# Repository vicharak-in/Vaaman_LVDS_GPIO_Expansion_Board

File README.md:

# Vaaman_UART_Expansion_Board

GPIO HAT 1:

LVDS RX and TX from Vaaman configure as a GPIO of this HAT. total 80 GPIOs are availabe in HAT can be configure form Vaaman LVDS.

voltage level of signal: 3.3V

Level translator Part number: TXB0108DQSR

LVDS connector part number: DF40C-60DP-0.4V(51)

Vaaman and HAT Connection: Flex cable

Power input: Vaaman Header 

NOT tested Yet(GPIO HAT 1).

GPIO HAT 2:

LVDS RX and TX from Vaaman configure as a GPIO of this HAT. total 80 GPIOs are availabe in HAT can be configure form Vaaman LVDS.

voltage level of signal: 3.3V & 1.8V (using jumper)

Level translator Part number: TXB0108DQSR

LVDS connector part number: DF40C-60DP-0.4V(51)

Vaaman and HAT Connection: Flex cable

Power input: Vaaman Header or Type-C 

Power up instructions:

Vaaman LVDS GPIO HAT can Power by two Options: 

Option 1: Using Female to Female Jumper From Vaaman Header to GPIO Hat Header

Vaaman Header 5V and GND:

GPIO HAT Header:

Working Properly.

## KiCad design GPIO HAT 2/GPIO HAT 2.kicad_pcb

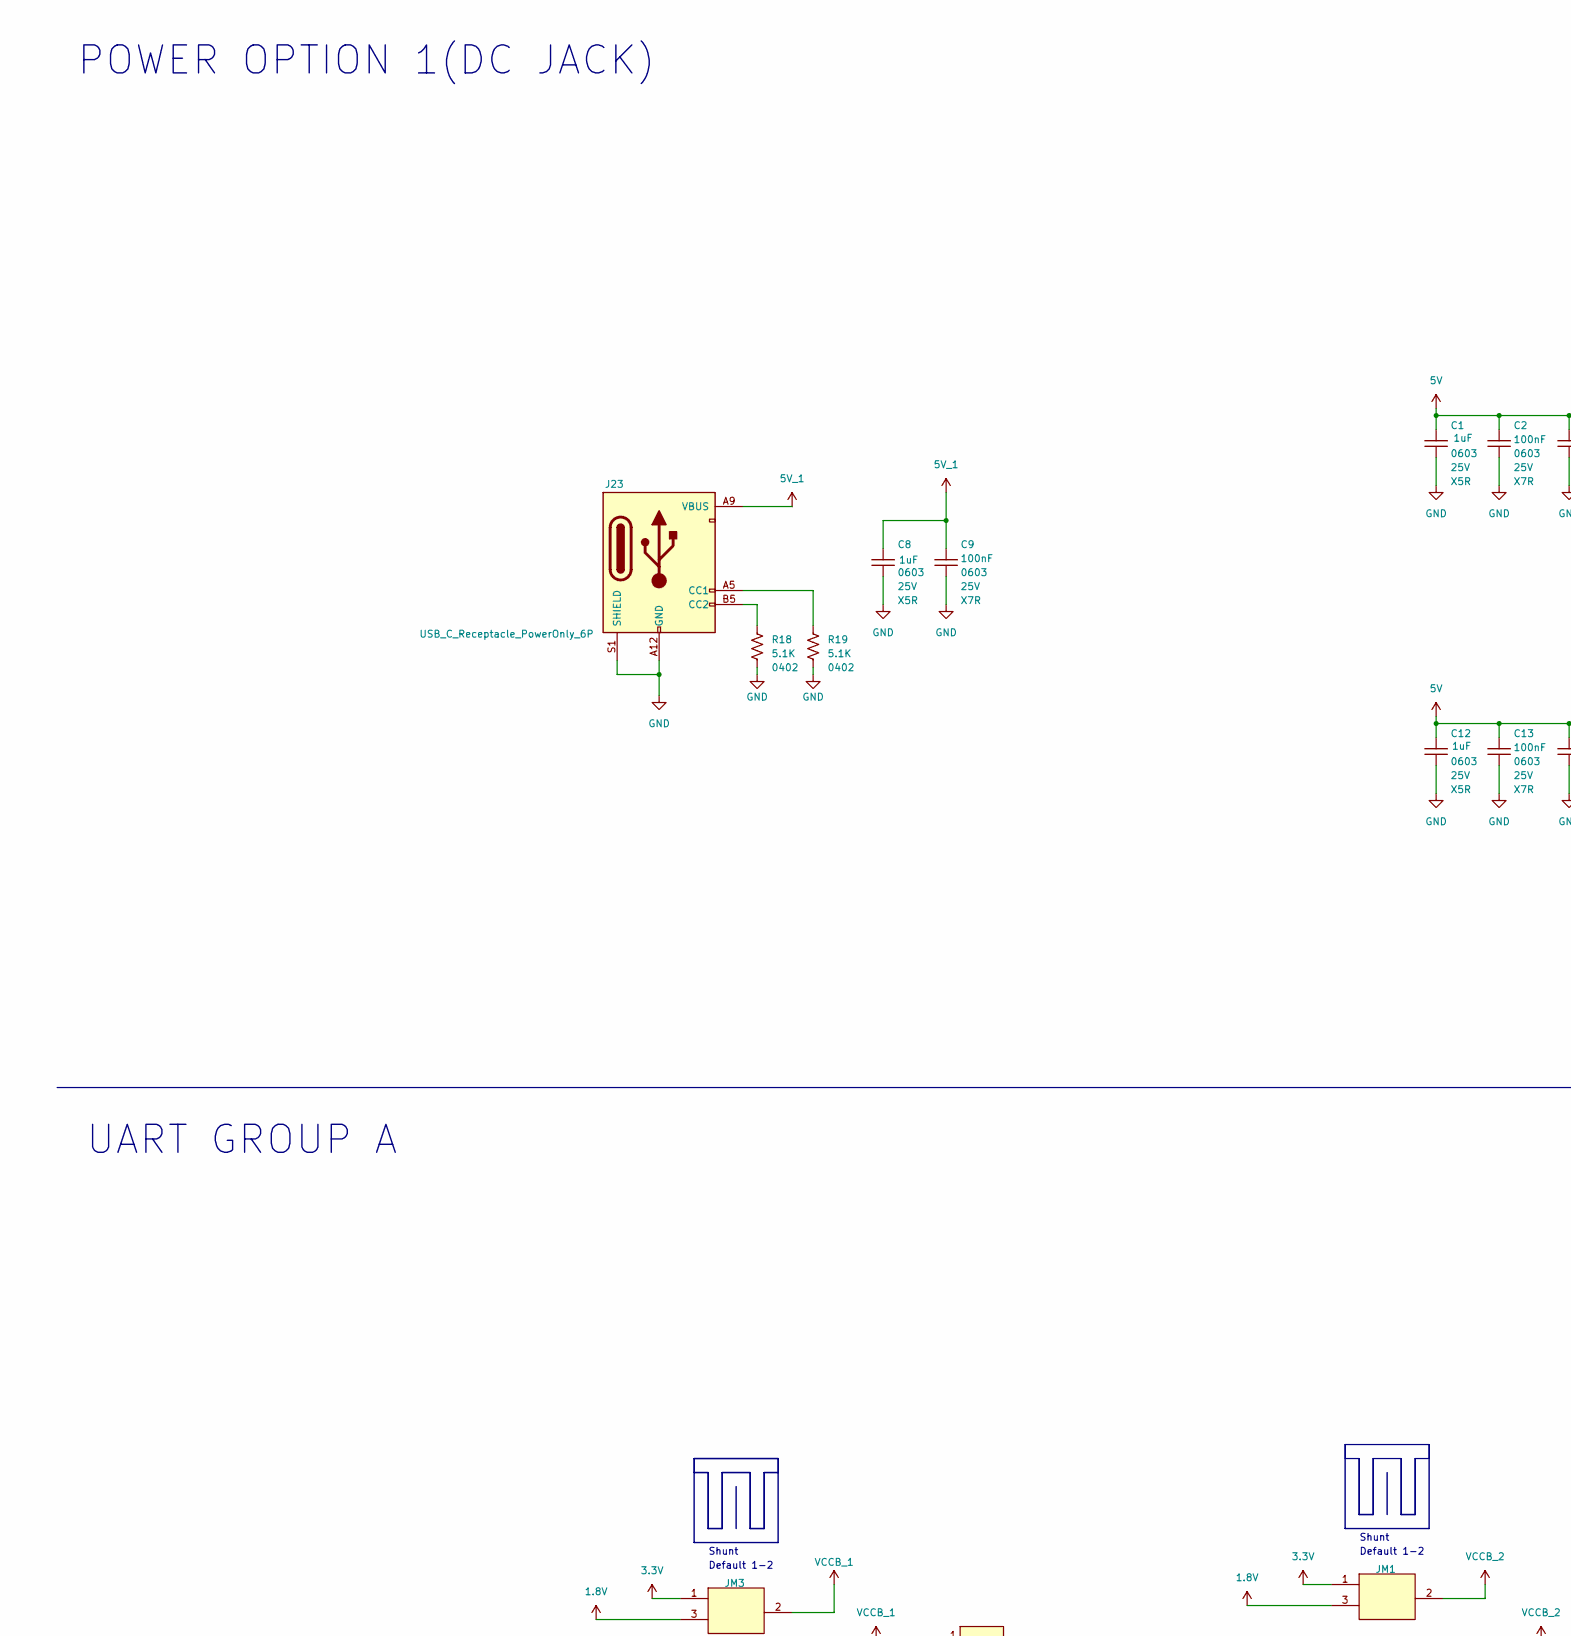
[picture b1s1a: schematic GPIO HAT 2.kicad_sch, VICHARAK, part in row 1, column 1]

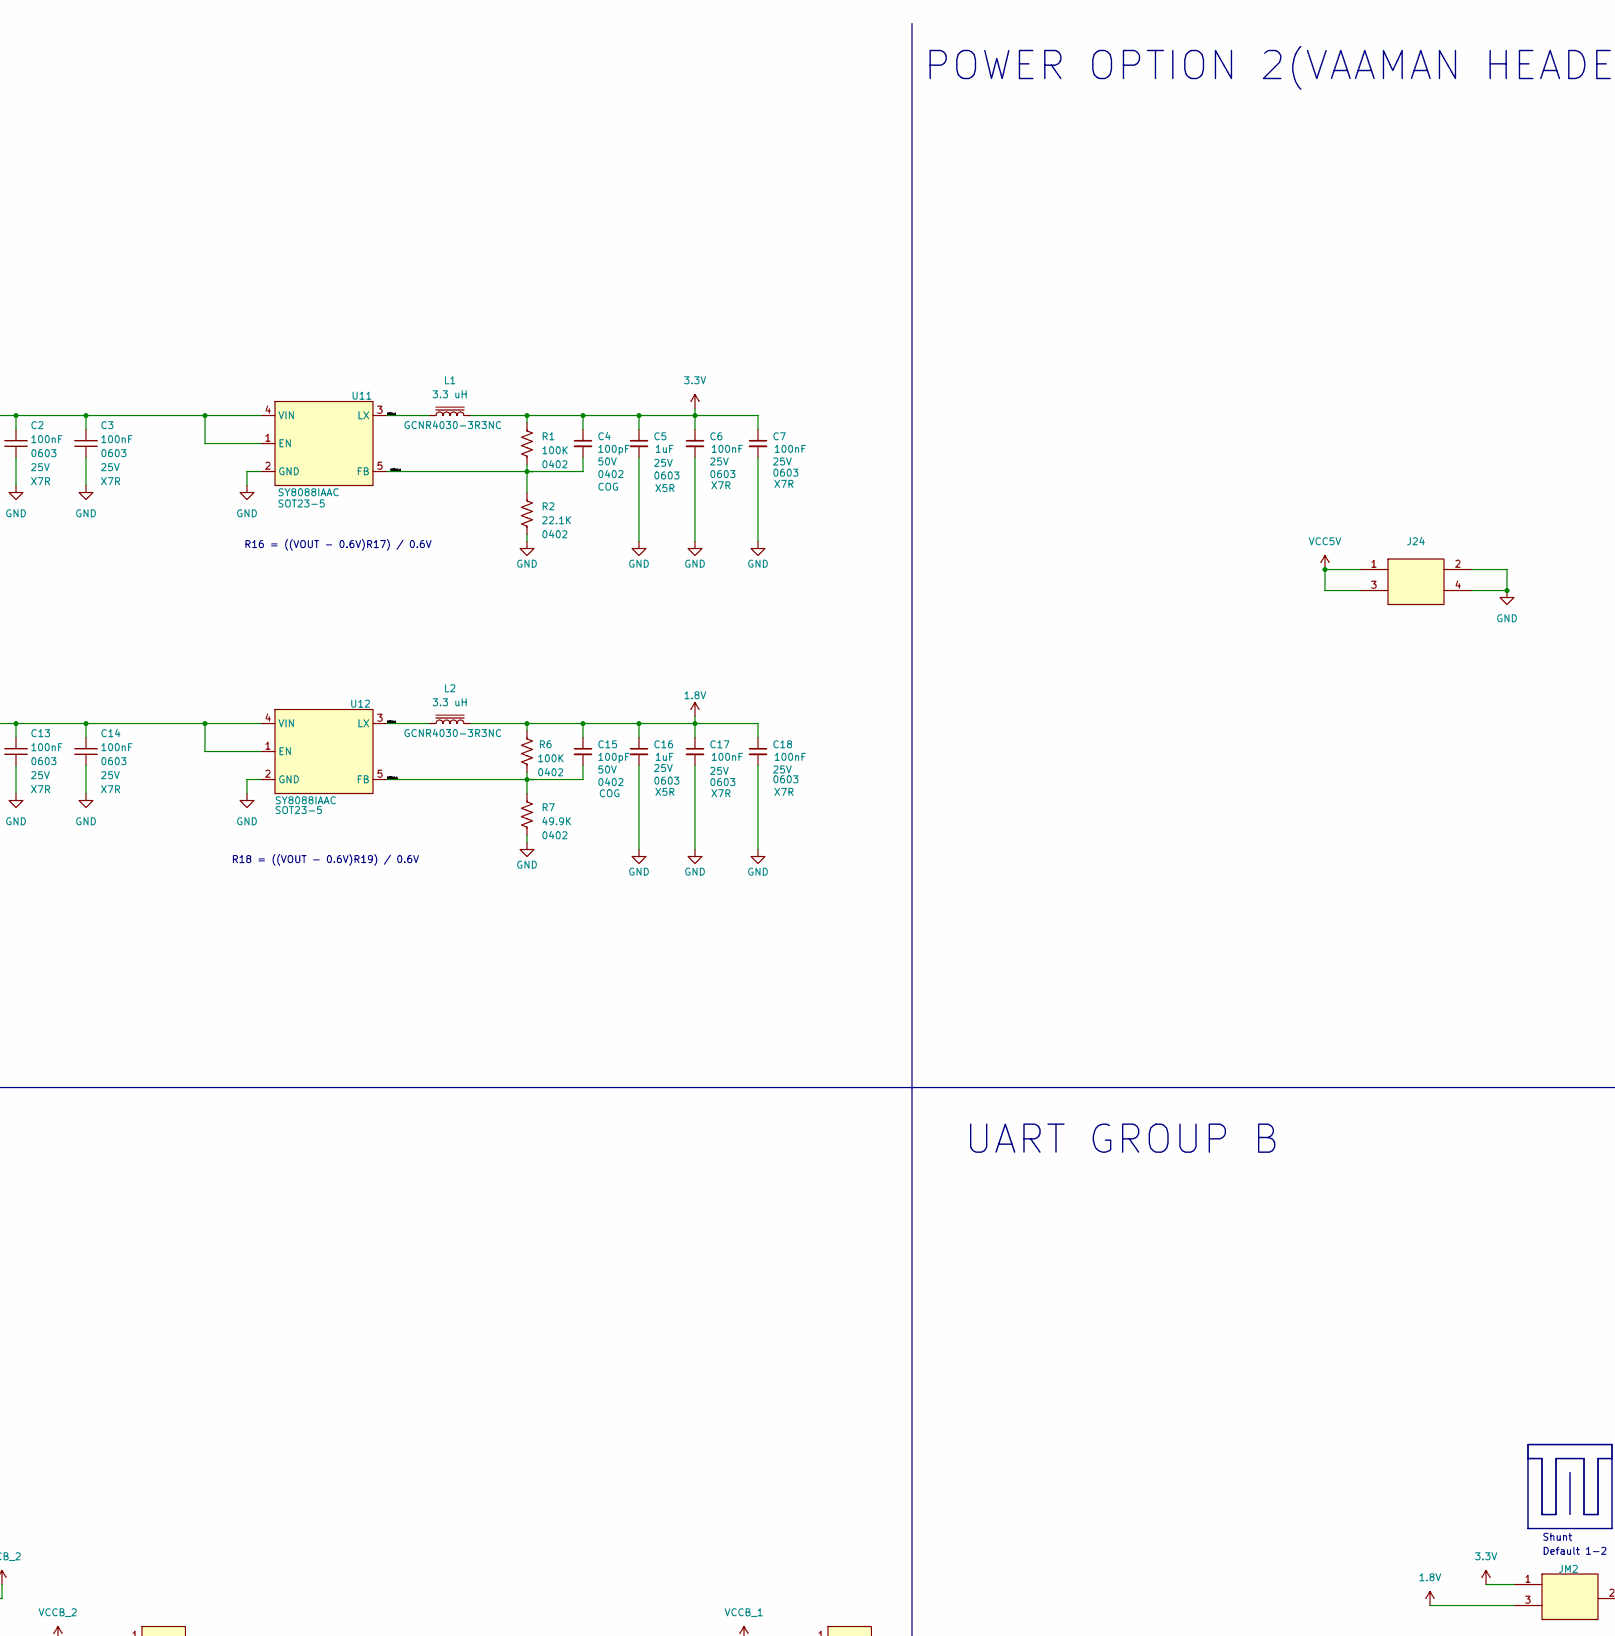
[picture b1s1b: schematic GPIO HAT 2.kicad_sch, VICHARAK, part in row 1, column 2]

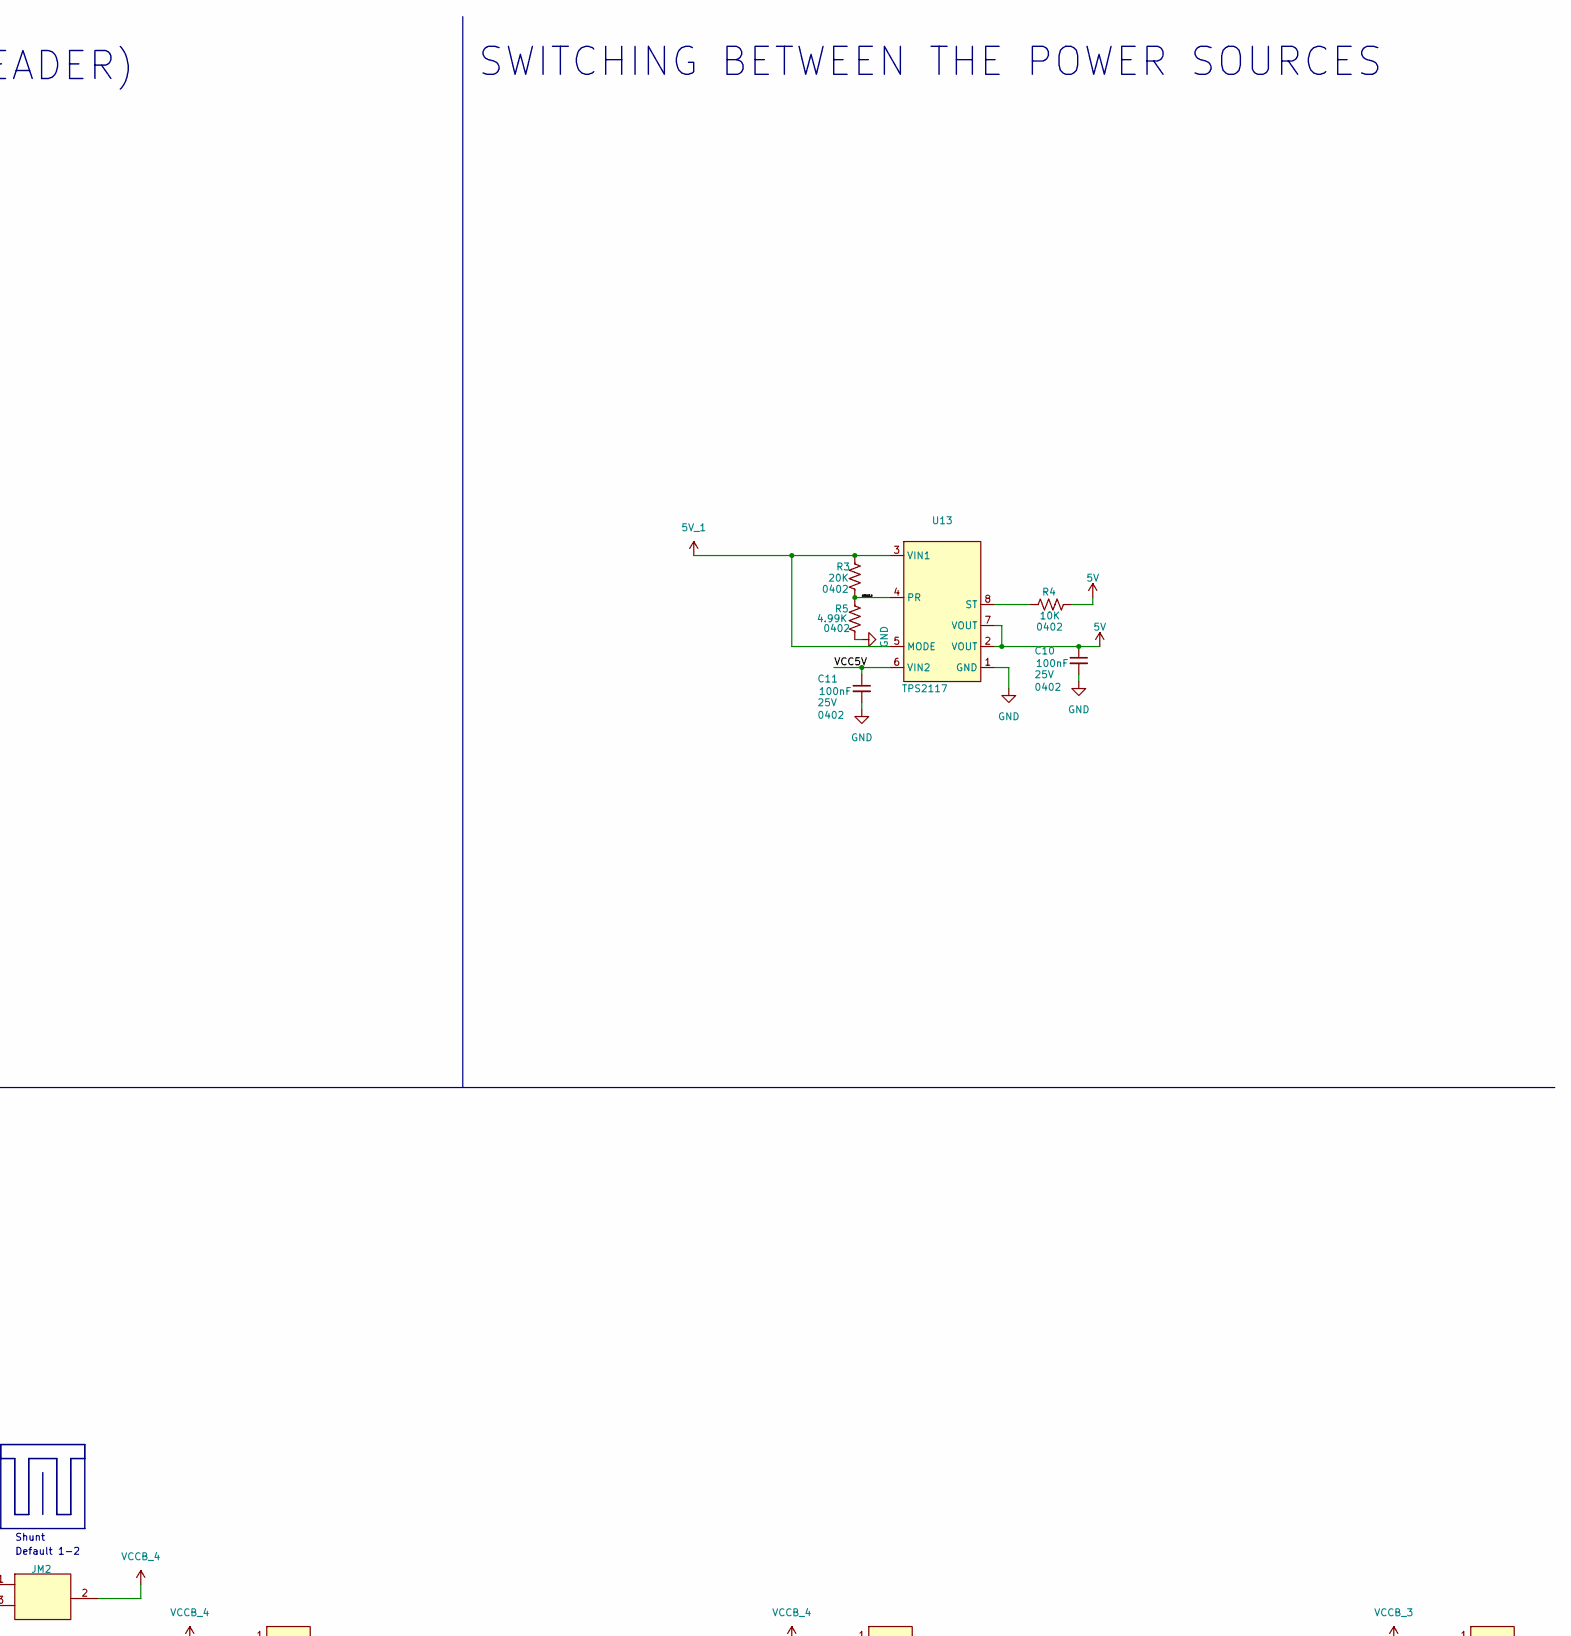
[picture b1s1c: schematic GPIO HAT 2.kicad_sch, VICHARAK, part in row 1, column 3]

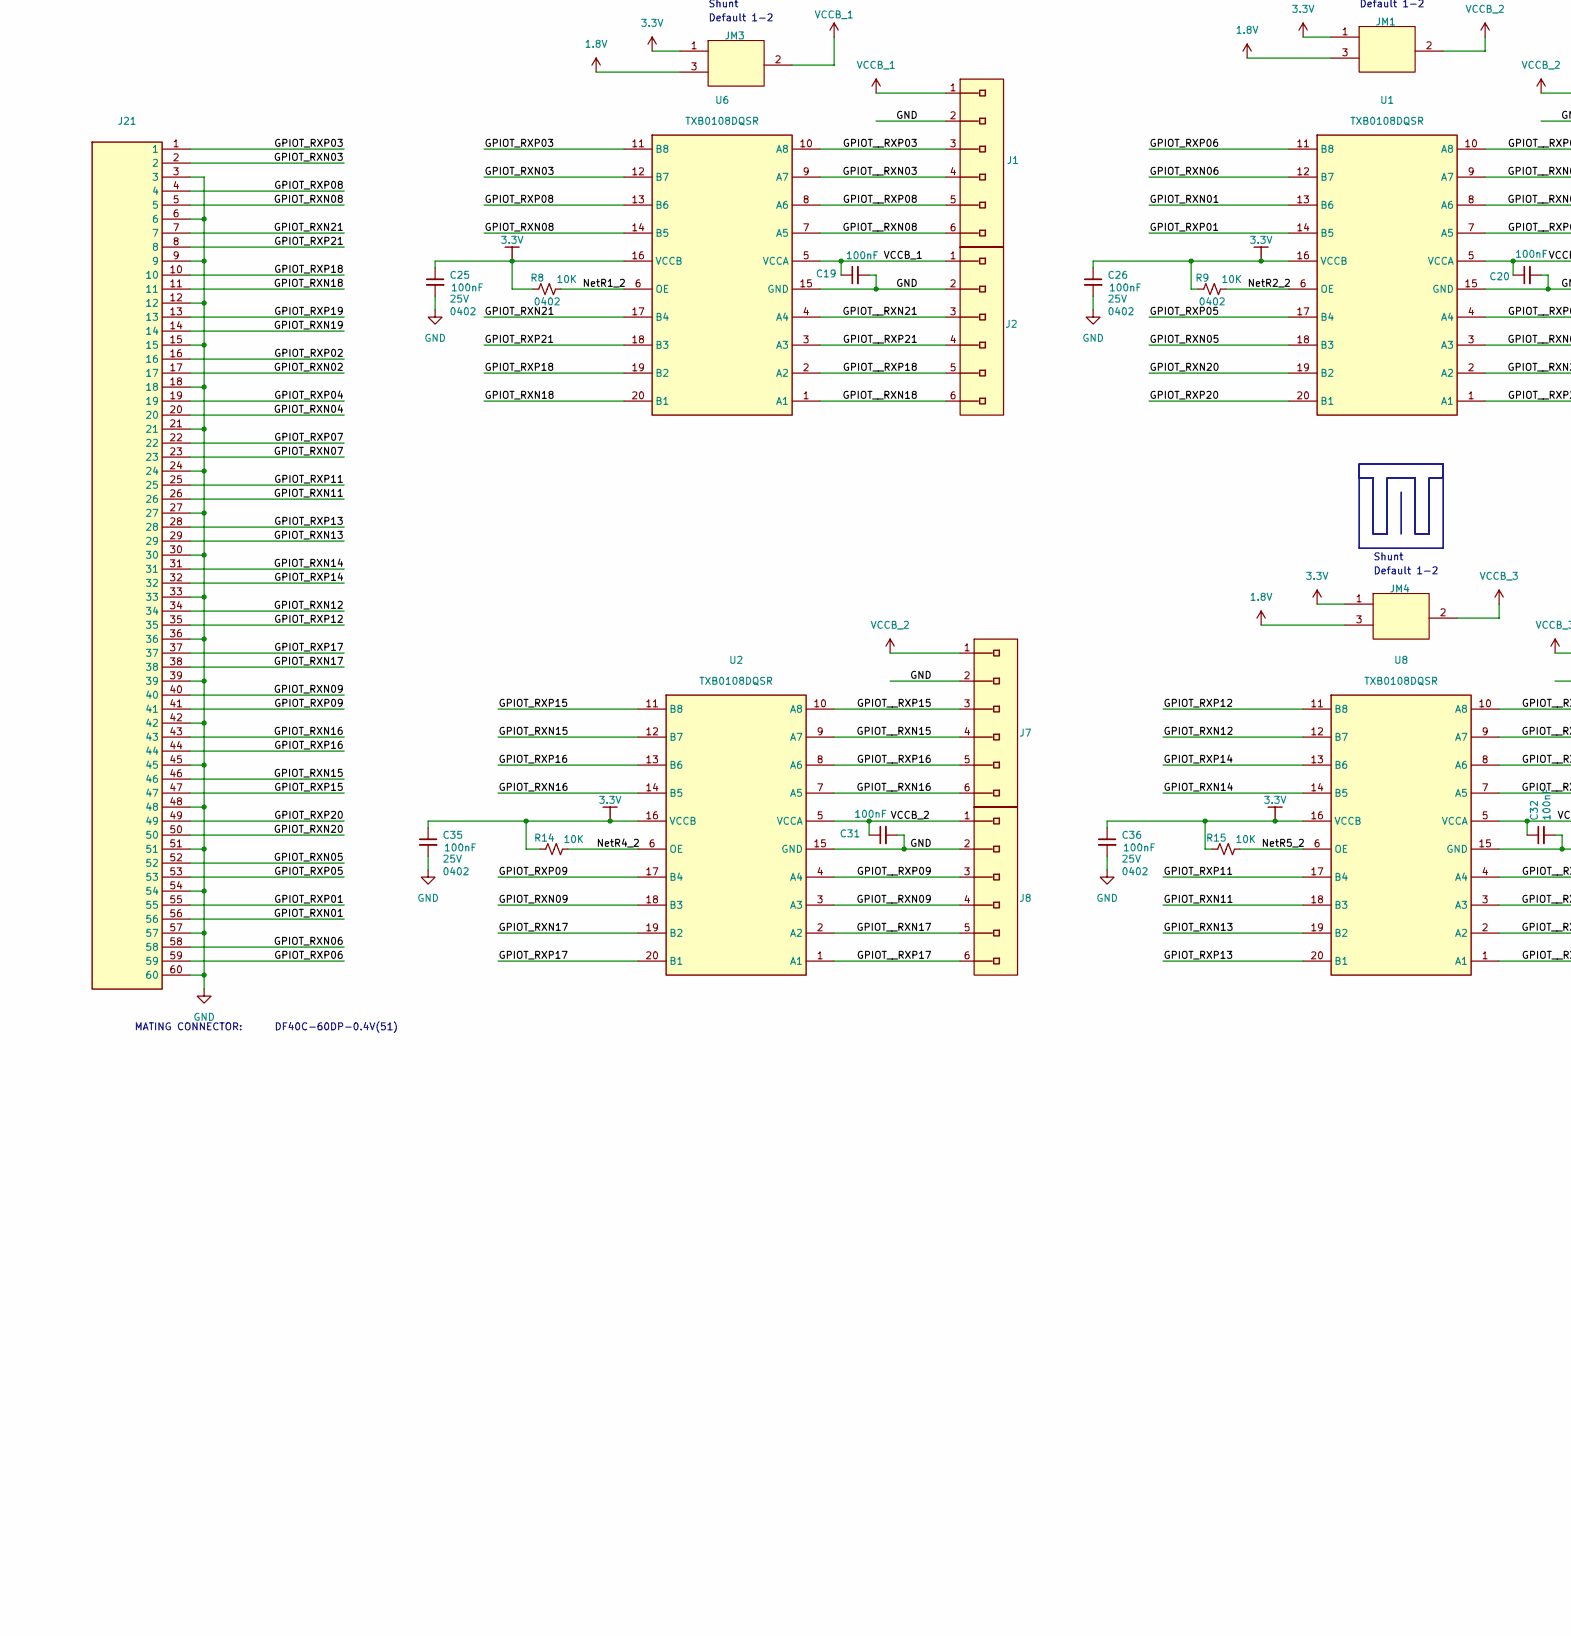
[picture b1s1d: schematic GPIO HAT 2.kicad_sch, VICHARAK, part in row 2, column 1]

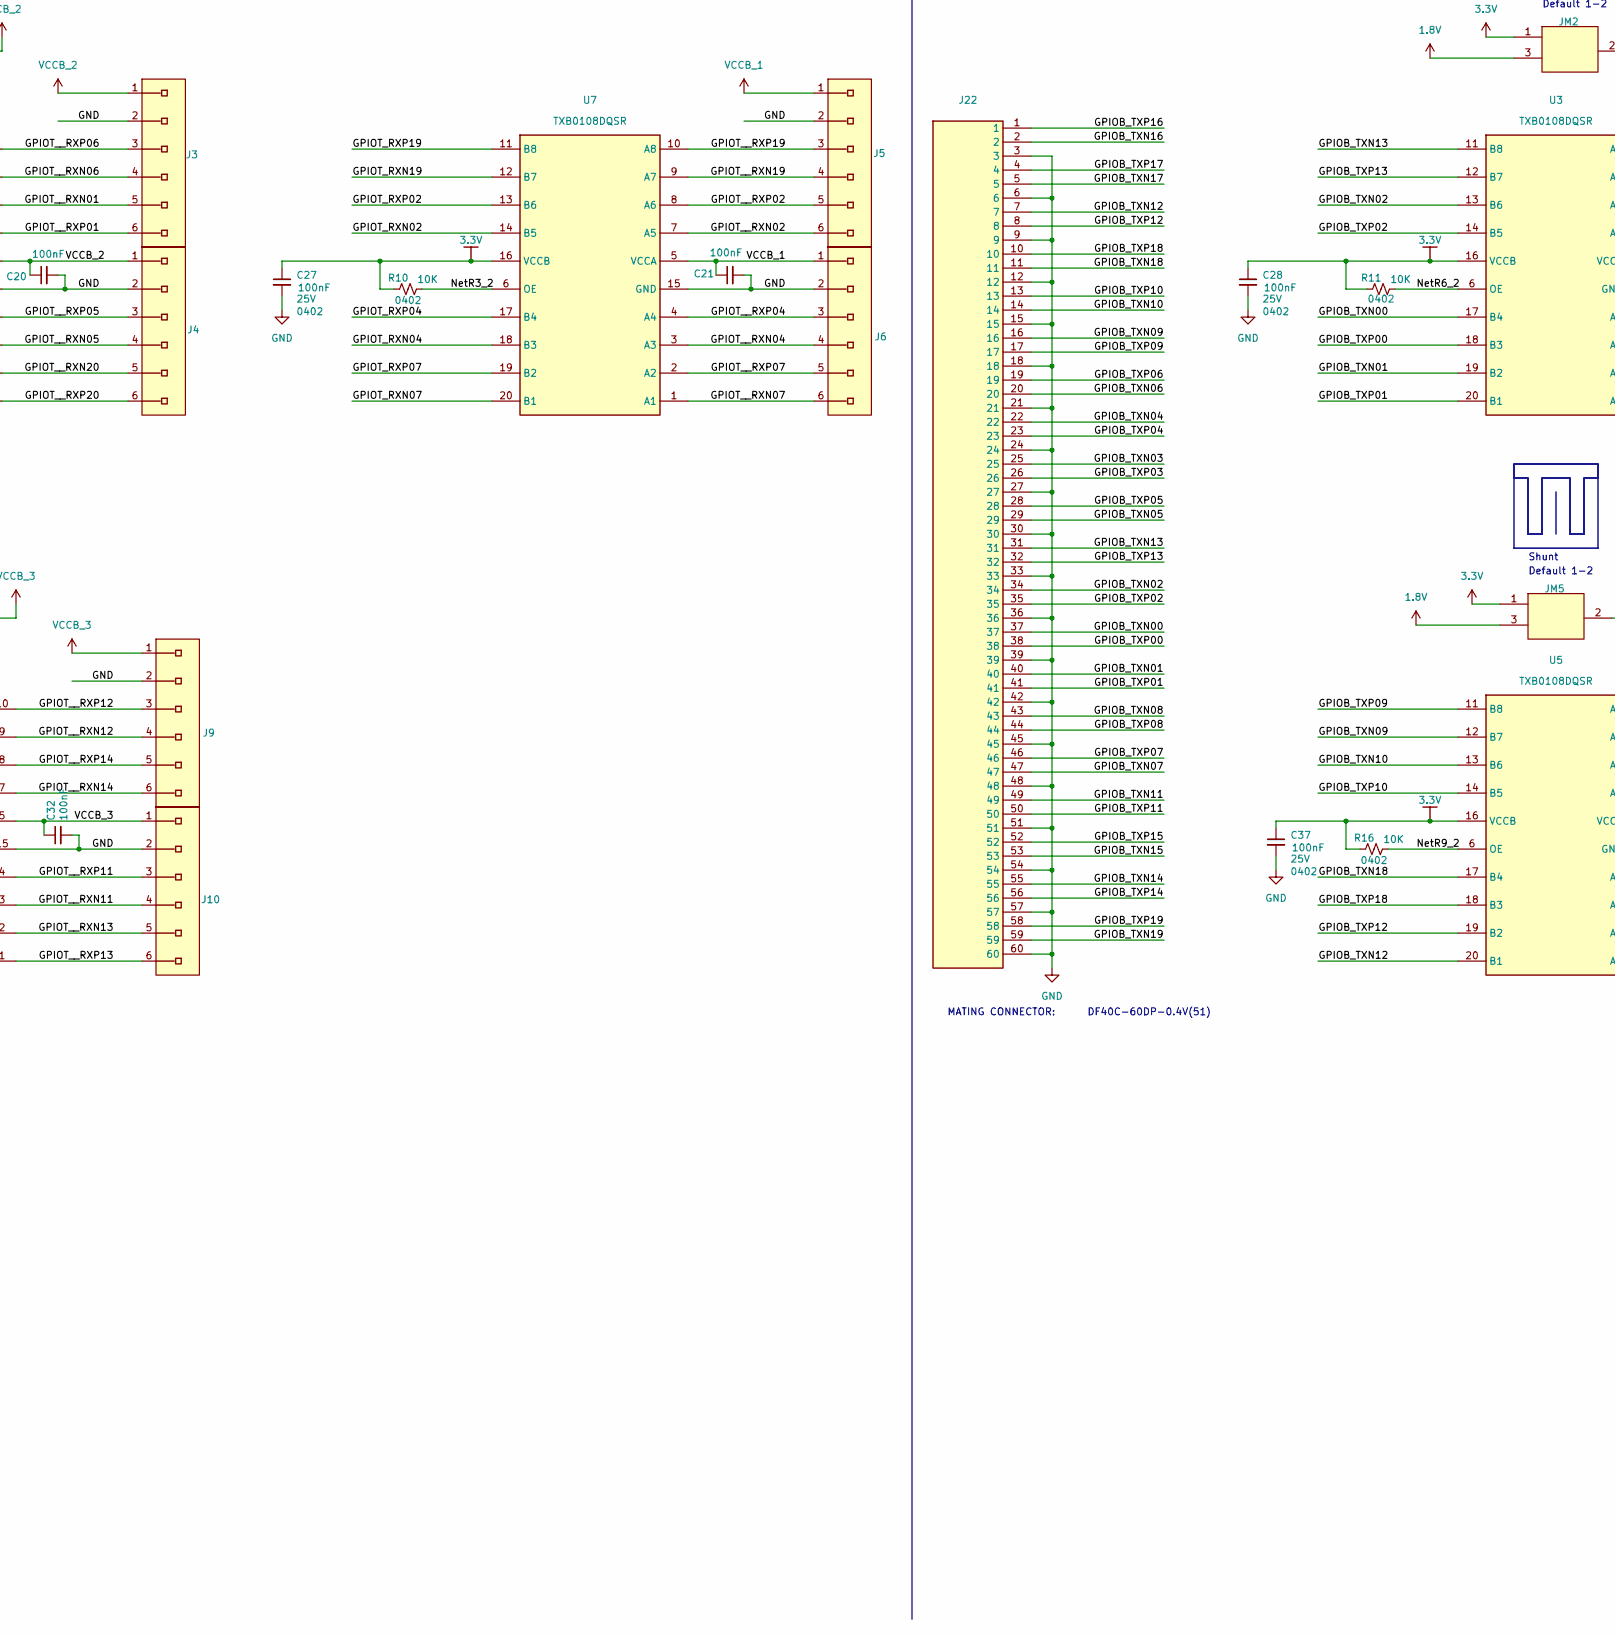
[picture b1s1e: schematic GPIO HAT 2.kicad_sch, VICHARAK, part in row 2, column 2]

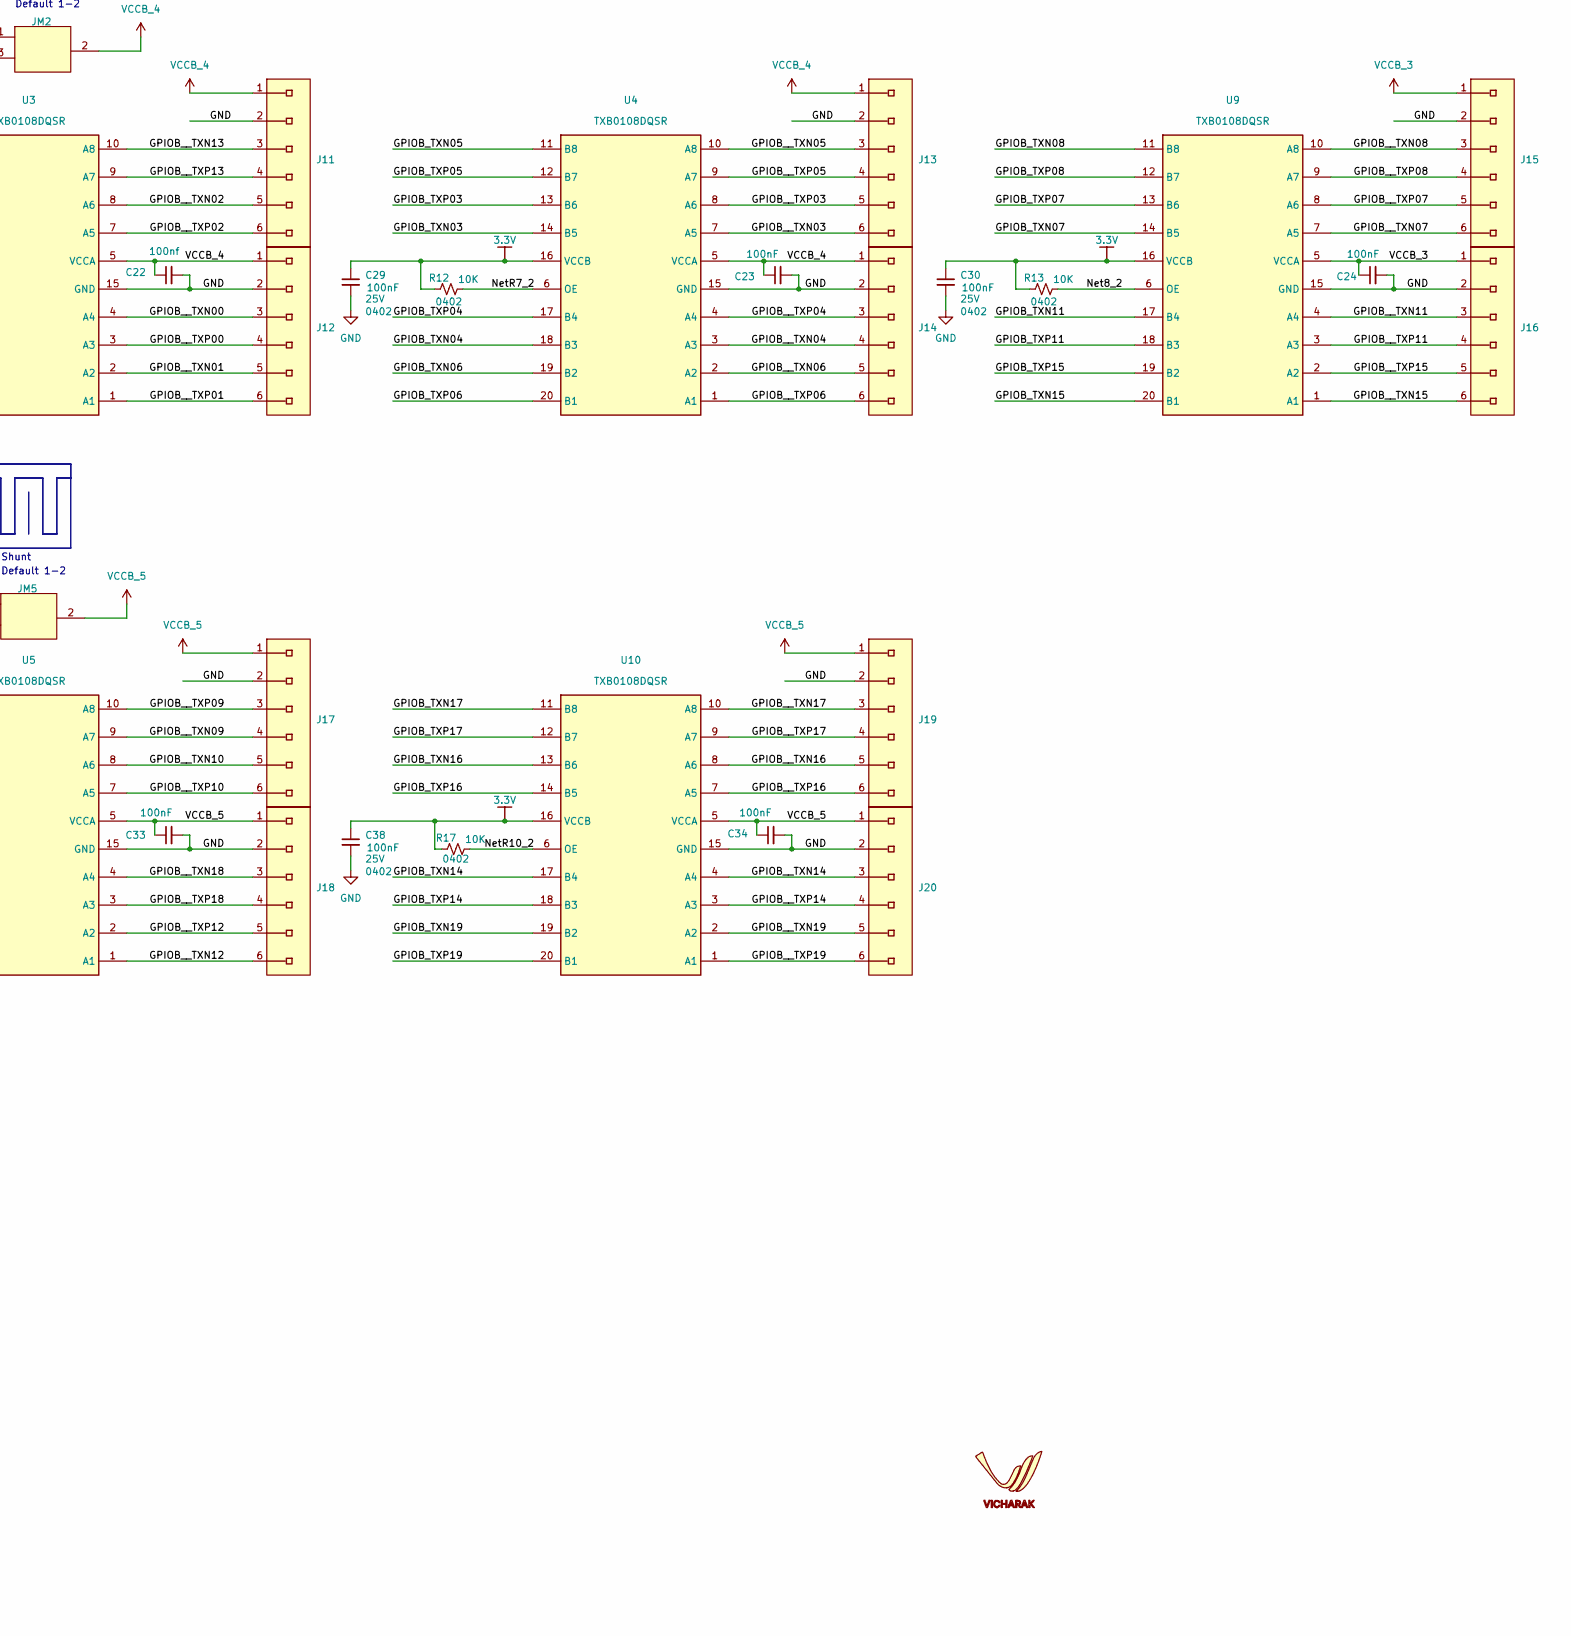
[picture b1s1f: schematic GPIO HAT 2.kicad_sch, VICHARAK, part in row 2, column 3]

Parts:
C1, C5, C8, C12, C16: 1uF; 0603_Cap; VOLTAGE 25V
C2, C3, C6, C7, C9, C13, C14, C17, C18: 100nF; 0603_Cap; VOLTAGE 25V
C4, C15: 100pF; 0402_Cap; VOLTAGE 50V
C10, C11, C19, C20, C21, C23, C24, C25, C26, C27, C28, C29, C30, C31, C32, C33, C34, C35, C36, C37, C38: 100nF; 0402_Cap; VOLTAGE 25V
C22: 100nf; 0402_Cap; VOLTAGE 25V
J1, J2, J3, J4, J5, J6, J7, J8, J9, J10, J11, J12, J13, J14, J15, J16, J17, J18, J19, J20: .; 01x06 HEADER
J21, J22: LVDS; Mouser Part Number 798-DF40C60DS0.4V51
J23: USB_C_Receptacle_PowerOnly_6P; USB_C_Receptacle_GCT_USB4125-xx-x-0190_6P_TopMnt_Horizontal; Manufacturer Part Number U262-061N-4BVC10
J24: 02x02; 02X02 HEADER
JM1, JM2, JM3, JM4, JM5: PinHeader_1x03_P2.54mm_Vertical
L1, L2: 3.3 uH; GCNR4030-3R3NC; Manufacturer Part Number GCNR4030-3R3NC
R1, R6: 100K; 0402_Res
R2: 22.1K; 0402_Res
R3: 20K; 0402_Res
R4, R8, R9, R10, R11, R12, R13, R14, R15, R16, R17: 10K; 0402_Res
R5: 4.99K; 0402_Res
R7: 49.9K; 0402_Res
R18, R19: 5.1K; 0402_Res
U1, U2, U3, U4, U5, U6, U7, U8, U9, U10: Manufacturer Part Number TXB0108DQSR
U11, U12: SY8088IAAC; Manufacturer Part Number SY8088IAAC
U13: TPS2117

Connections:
1.8V: C15.1, C16.1, C17.1, C18.1, JM1.3, JM2.3, JM3.3, JM4.3, JM5.3, L2.2, R6.1
3.3V: C4.1, C5.1, C6.1, C7.1, C25.1, C26.1, C27.1, C28.1, C29.1, C30.1, C35.1, C36.1, C37.1, C38.1, JM1.1, JM2.1, JM3.1, JM4.1, JM5.1, L1.2, R1.1, R8.1, R9.1, R10.1, R11.1, R12.1, R13.1, R14.1, R15.1, R16.1, R17.1, U1.16 (VCCB), U2.16 (VCCB), U3.16 (VCCB), U4.16 (VCCB), U5.16 (VCCB), U6.16 (VCCB), U7.16 (VCCB), U8.16 (VCCB), U9.16 (VCCB), U10.16 (VCCB)
5V: C1.1, C2.1, C3.1, C10.1, C12.1, C13.1, C14.1, R4.2, U11.1 (EN), U11.4 (VIN), U12.1 (EN), U12.4 (VIN), U13.2 (VOUT), U13.7 (VOUT)
5V_1: C8.1, C9.1, J23.A9 (VBUS), R3.2, U13.3 (VIN1), U13.5 (MODE)
/GPIOB_TXN00: J22.37, U3.17 (B4)
/GPIOB_TXN01: J22.40, U3.19 (B2)
/GPIOB_TXN02: J22.34, U3.13 (B6)
/GPIOB_TXN03: J22.25, U4.14 (B5)
/GPIOB_TXN04: J22.22, U4.18 (B3)
/GPIOB_TXN05: J22.29, U4.11 (B8)
/GPIOB_TXN06: J22.20, U4.19 (B2)
/GPIOB_TXN07: J22.47, U9.14 (B5)
/GPIOB_TXN08: J22.43, U9.11 (B8)
/GPIOB_TXN09: J22.16, U5.12 (B7)
/GPIOB_TXN10: J22.14, U5.13 (B6)
/GPIOB_TXN11: J22.49, U9.17 (B4)
/GPIOB_TXN12: J22.7, U5.20 (B1)
/GPIOB_TXN13: J22.31, U3.11 (B8)
/GPIOB_TXN14: J22.55, U10.17 (B4)
/GPIOB_TXN15: J22.53, U9.20 (B1)
/GPIOB_TXN16: J22.2, U10.13 (B6)
/GPIOB_TXN17: J22.5, U10.11 (B8)
/GPIOB_TXN18: J22.11, U5.17 (B4)
/GPIOB_TXN19: J22.59, U10.19 (B2)
/GPIOB_TXP00: J22.38, U3.18 (B3)
/GPIOB_TXP01: J22.41, U3.20 (B1)
/GPIOB_TXP02: J22.35, U3.14 (B5)
/GPIOB_TXP03: J22.26, U4.13 (B6)
/GPIOB_TXP04: J22.23, U4.17 (B4)
/GPIOB_TXP05: J22.28, U4.12 (B7)
/GPIOB_TXP06: J22.19, U4.20 (B1)
/GPIOB_TXP07: J22.46, U9.13 (B6)
/GPIOB_TXP08: J22.44, U9.12 (B7)
/GPIOB_TXP09: J22.17, U5.11 (B8)
/GPIOB_TXP10: J22.13, U5.14 (B5)
/GPIOB_TXP11: J22.50, U9.18 (B3)
/GPIOB_TXP12: J22.8, U5.19 (B2)
/GPIOB_TXP13: J22.32, U3.12 (B7)
/GPIOB_TXP14: J22.56, U10.18 (B3)
/GPIOB_TXP15: J22.52, U9.19 (B2)
/GPIOB_TXP16: J22.1, U10.14 (B5)
/GPIOB_TXP17: J22.4, U10.12 (B7)
/GPIOB_TXP18: J22.10, U5.18 (B3)
/GPIOB_TXP19: J22.58, U10.20 (B1)
/GPIOB__TXN00: J12.3, U3.4 (A4)
/GPIOB__TXN01: J12.5 (4), U3.2 (A2)
/GPIOB__TXN02: J11.5 (4), U3.8 (A6)
/GPIOB__TXN03: J13.6, U4.7 (A5)
/GPIOB__TXN04: J14.4, U4.3 (A3)
/GPIOB__TXN05: J13.3, U4.10 (A8)
/GPIOB__TXN06: J14.5 (4), U4.2 (A2)
/GPIOB__TXN07: J15.6, U9.7 (A5)
/GPIOB__TXN08: J15.3, U9.10 (A8)
/GPIOB__TXN09: J17.4, U5.9 (A7)
/GPIOB__TXN10: J17.5 (4), U5.8 (A6)
/GPIOB__TXN11: J16.3, U9.4 (A4)
/GPIOB__TXN12: J18.6, U5.1 (A1)
/GPIOB__TXN13: J11.3, U3.10 (A8)
/GPIOB__TXN14: J20.3, U10.4 (A4)
/GPIOB__TXN15: J16.6, U9.1 (A1)
/GPIOB__TXN16: J19.5 (4), U10.8 (A6)
/GPIOB__TXN17: J19.3, U10.10 (A8)
/GPIOB__TXN18: J18.3, U5.4 (A4)
/GPIOB__TXN19: J20.5 (4), U10.2 (A2)
/GPIOB__TXP00: J12.4, U3.3 (A3)
/GPIOB__TXP01: J12.6, U3.1 (A1)
/GPIOB__TXP02: J11.6, U3.7 (A5)
/GPIOB__TXP03: J13.5 (4), U4.8 (A6)
/GPIOB__TXP04: J14.3, U4.4 (A4)
/GPIOB__TXP05: J13.4, U4.9 (A7)
/GPIOB__TXP06: J14.6, U4.1 (A1)
/GPIOB__TXP07: J15.5 (4), U9.8 (A6)
/GPIOB__TXP08: J15.4, U9.9 (A7)
/GPIOB__TXP09: J17.3, U5.10 (A8)
/GPIOB__TXP10: J17.6, U5.7 (A5)
/GPIOB__TXP11: J16.4, U9.3 (A3)
/GPIOB__TXP12: J18.5 (4), U5.2 (A2)
/GPIOB__TXP13: J11.4, U3.9 (A7)
/GPIOB__TXP14: J20.4, U10.3 (A3)
/GPIOB__TXP15: J16.5 (4), U9.2 (A2)
/GPIOB__TXP16: J19.6, U10.7 (A5)
/GPIOB__TXP17: J19.4, U10.9 (A7)
/GPIOB__TXP18: J18.4, U5.3 (A3)
/GPIOB__TXP19: J20.6, U10.1 (A1)
/GPIOT_RXN01: J21.56, U1.13 (B6)
/GPIOT_RXN02: J21.17, U7.14 (B5)
/GPIOT_RXN03: J21.2, U6.12 (B7)
/GPIOT_RXN04: J21.20, U7.18 (B3)
/GPIOT_RXN05: J21.52, U1.18 (B3)
/GPIOT_RXN06: J21.58, U1.12 (B7)
/GPIOT_RXN07: J21.23, U7.20 (B1)
/GPIOT_RXN08: J21.5, U6.14 (B5)
/GPIOT_RXN09: J21.40, U2.18 (B3)
/GPIOT_RXN11: J21.26, U8.18 (B3)
/GPIOT_RXN12: J21.34, U8.12 (B7)
/GPIOT_RXN13: J21.29, U8.19 (B2)
/GPIOT_RXN14: J21.31, U8.14 (B5)
/GPIOT_RXN15: J21.46, U2.12 (B7)
/GPIOT_RXN16: J21.43, U2.14 (B5)
/GPIOT_RXN17: J21.38, U2.19 (B2)
/GPIOT_RXN18: J21.11, U6.20 (B1)
/GPIOT_RXN19: J21.14, U7.12 (B7)
/GPIOT_RXN20: J21.50, U1.19 (B2)
/GPIOT_RXN21: J21.7, U6.17 (B4)
/GPIOT_RXP01: J21.55, U1.14 (B5)
/GPIOT_RXP02: J21.16, U7.13 (B6)
/GPIOT_RXP03: J21.1, U6.11 (B8)
/GPIOT_RXP04: J21.19, U7.17 (B4)
/GPIOT_RXP05: J21.53, U1.17 (B4)
/GPIOT_RXP06: J21.59, U1.11 (B8)
/GPIOT_RXP07: J21.22, U7.19 (B2)
/GPIOT_RXP08: J21.4, U6.13 (B6)
/GPIOT_RXP09: J21.41, U2.17 (B4)
/GPIOT_RXP11: J21.25, U8.17 (B4)
/GPIOT_RXP12: J21.35, U8.11 (B8)
/GPIOT_RXP13: J21.28, U8.20 (B1)
/GPIOT_RXP14: J21.32, U8.13 (B6)
/GPIOT_RXP15: J21.47, U2.11 (B8)
/GPIOT_RXP16: J21.44, U2.13 (B6)
/GPIOT_RXP17: J21.37, U2.20 (B1)
/GPIOT_RXP18: J21.10, U6.19 (B2)
/GPIOT_RXP19: J21.13, U7.11 (B8)
/GPIOT_RXP20: J21.49, U1.20 (B1)
/GPIOT_RXP21: J21.8, U6.18 (B3)
/GPIOT__RXN01: J3.5 (4), U1.8 (A6)
/GPIOT__RXN02: J5.6, U7.7 (A5)
/GPIOT__RXN03: J1.4, U6.9 (A7)
/GPIOT__RXN04: J6.4, U7.3 (A3)
/GPIOT__RXN05: J4.4, U1.3 (A3)
/GPIOT__RXN06: J3.4, U1.9 (A7)
/GPIOT__RXN07: J6.6, U7.1 (A1)
/GPIOT__RXN08: J1.6, U6.7 (A5)
/GPIOT__RXN09: J8.4, U2.3 (A3)
/GPIOT__RXN11: J10.4, U8.3 (A3)
/GPIOT__RXN12: J9.4, U8.9 (A7)
/GPIOT__RXN13: J10.5 (4), U8.2 (A2)
/GPIOT__RXN14: J9.6, U8.7 (A5)
/GPIOT__RXN15: J7.4, U2.9 (A7)
/GPIOT__RXN16: J7.6, U2.7 (A5)
/GPIOT__RXN17: J8.5 (4), U2.2 (A2)
/GPIOT__RXN18: J2.6, U6.1 (A1)
/GPIOT__RXN19: J5.4, U7.9 (A7)
/GPIOT__RXN20: J4.5 (4), U1.2 (A2)
/GPIOT__RXN21: J2.3, U6.4 (A4)
/GPIOT__RXP01: J3.6, U1.7 (A5)
/GPIOT__RXP02: J5.5 (4), U7.8 (A6)
/GPIOT__RXP03: J1.3, U6.10 (A8)
/GPIOT__RXP04: J6.3, U7.4 (A4)
/GPIOT__RXP05: J4.3, U1.4 (A4)
/GPIOT__RXP06: J3.3, U1.10 (A8)
/GPIOT__RXP07: J6.5 (4), U7.2 (A2)
/GPIOT__RXP08: J1.5 (4), U6.8 (A6)
/GPIOT__RXP09: J8.3, U2.4 (A4)
/GPIOT__RXP11: J10.3, U8.4 (A4)
/GPIOT__RXP12: J9.3, U8.10 (A8)
/GPIOT__RXP13: J10.6, U8.1 (A1)
/GPIOT__RXP14: J9.5 (4), U8.8 (A6)
/GPIOT__RXP15: J7.3, U2.10 (A8)
/GPIOT__RXP16: J7.5 (4), U2.8 (A6)
/GPIOT__RXP17: J8.6, U2.1 (A1)
/GPIOT__RXP18: J2.5 (4), U6.2 (A2)
/GPIOT__RXP19: J5.3, U7.10 (A8)
/GPIOT__RXP20: J4.6, U1.1 (A1)
/GPIOT__RXP21: J2.4, U6.3 (A3)
/NETL1_1: L1.1, U11.3 (LX)
/NETL3_1: L2.1, U12.3 (LX)
/NETR16_1: C4.2, R1.2, R2.1, U11.5 (FB)
/NETR18_1: C15.2, R6.2, R7.1, U12.5 (FB)
/NETR20_2: R3.1, R5.2, U13.4 (PR)
/Net8_2: R13.2, U9.6 (OE)
/NetR1_2: R8.2, U6.6 (OE)
/NetR2_2: R9.2, U1.6 (OE)
/NetR3_2: R10.2, U7.6 (OE)
/NetR4_2: R14.2, U2.6 (OE)
/NetR5_2: R15.2, U8.6 (OE)
/NetR6_2: R11.2, U3.6 (OE)
/NetR7_2: R12.2, U4.6 (OE)
/NetR9_2: R16.2, U5.6 (OE)
/NetR10_2: R17.2, U10.6 (OE)
GND: C1.2, C2.2, C3.2, C5.2, C6.2, C7.2, C8.2, C9.2, C10.2, C11.2, C12.2, C13.2, C14.2, C16.2, C17.2, C18.2, C19.2, C20.2, C21.2, C22.2, C23.2, C24.2, C25.2, C26.2, C27.2, C28.2, C29.2, C30.2, C31.2, C32.2, C33.2, C34.2, C35.2, C36.2, C37.2, C38.2, J1.2, J2.2, J3.2, J4.2, J5.2, J6.2, J7.2, J8.2, J9.2, J10.2, J11.2, J12.2, J13.2, J14.2, J15.2, J16.2, J17.2, J18.2, J19.2, J20.2, J21.3, J21.6, J21.9, J21.12, J21.15, J21.18, J21.21, J21.24, J21.27, J21.30, J21.33, J21.36, J21.39, J21.42, J21.45, J21.48, J21.51, J21.54, J21.57, J21.60, J22.3, J22.6, J22.9, J22.12, J22.15, J22.18, J22.21, J22.24, J22.27, J22.30, J22.33, J22.36, J22.39, J22.42, J22.45, J22.48, J22.51, J22.54, J22.57, J22.60, J23.A12 (GND), J23.B12 (GND), J23.S1 (SHIELD), J24.2, J24.4 (3), R2.2, R5.1, R7.2, R18.2, R19.2, U1.15 (GND), U2.15 (GND), U3.15 (GND), U4.15 (GND), U5.15 (GND), U6.15 (GND), U7.15 (GND), U8.15 (GND), U9.15 (GND), U10.15 (GND), U11.2 (GND), U12.2 (GND), U13.1 (GND)
unnamed: J23.A5 (CC1), R19.1
unnamed: J23.B5 (CC2), R18.1
unnamed: R4.1, U13.8 (ST)
VCC5V: C11.1, J24.1, J24.3, U13.6 (VIN2)
VCCB_1: C19.1, C21.1, J1.1, J2.1, J5.1, J6.1, JM3.2, U6.5 (VCCA), U7.5 (VCCA)
VCCB_2: C20.1, C31.1, J3.1, J4.1, J7.1, J8.1, JM1.2, U1.5 (VCCA), U2.5 (VCCA)
VCCB_3: C24.1, C32.1, J9.1, J10.1, J15.1, J16.1, JM4.2, U8.5 (VCCA), U9.5 (VCCA)
VCCB_4: C22.1, C23.1, J11.1, J12.1, J13.1, J14.1, JM2.2, U3.5 (VCCA), U4.5 (VCCA)
VCCB_5: C33.1, C34.1, J17.1, J18.1, J19.1, J20.1, JM5.2, U5.5 (VCCA), U10.5 (VCCA)

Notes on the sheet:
DF40C-60DP-0.4V(51)
UART GROUP B
POWER OPTION 1(DC JACK)
MATING CONNECTOR:
Shunt
Default 1-2
R18 = ((VOUT - 0.6V)R19) / 0.6V
POWER OPTION 2(VAAMAN HEADER)
R16 = ((VOUT - 0.6V)R17) / 0.6V
UART GROUP A
SWITCHING BETWEEN THE POWER SOURCES
